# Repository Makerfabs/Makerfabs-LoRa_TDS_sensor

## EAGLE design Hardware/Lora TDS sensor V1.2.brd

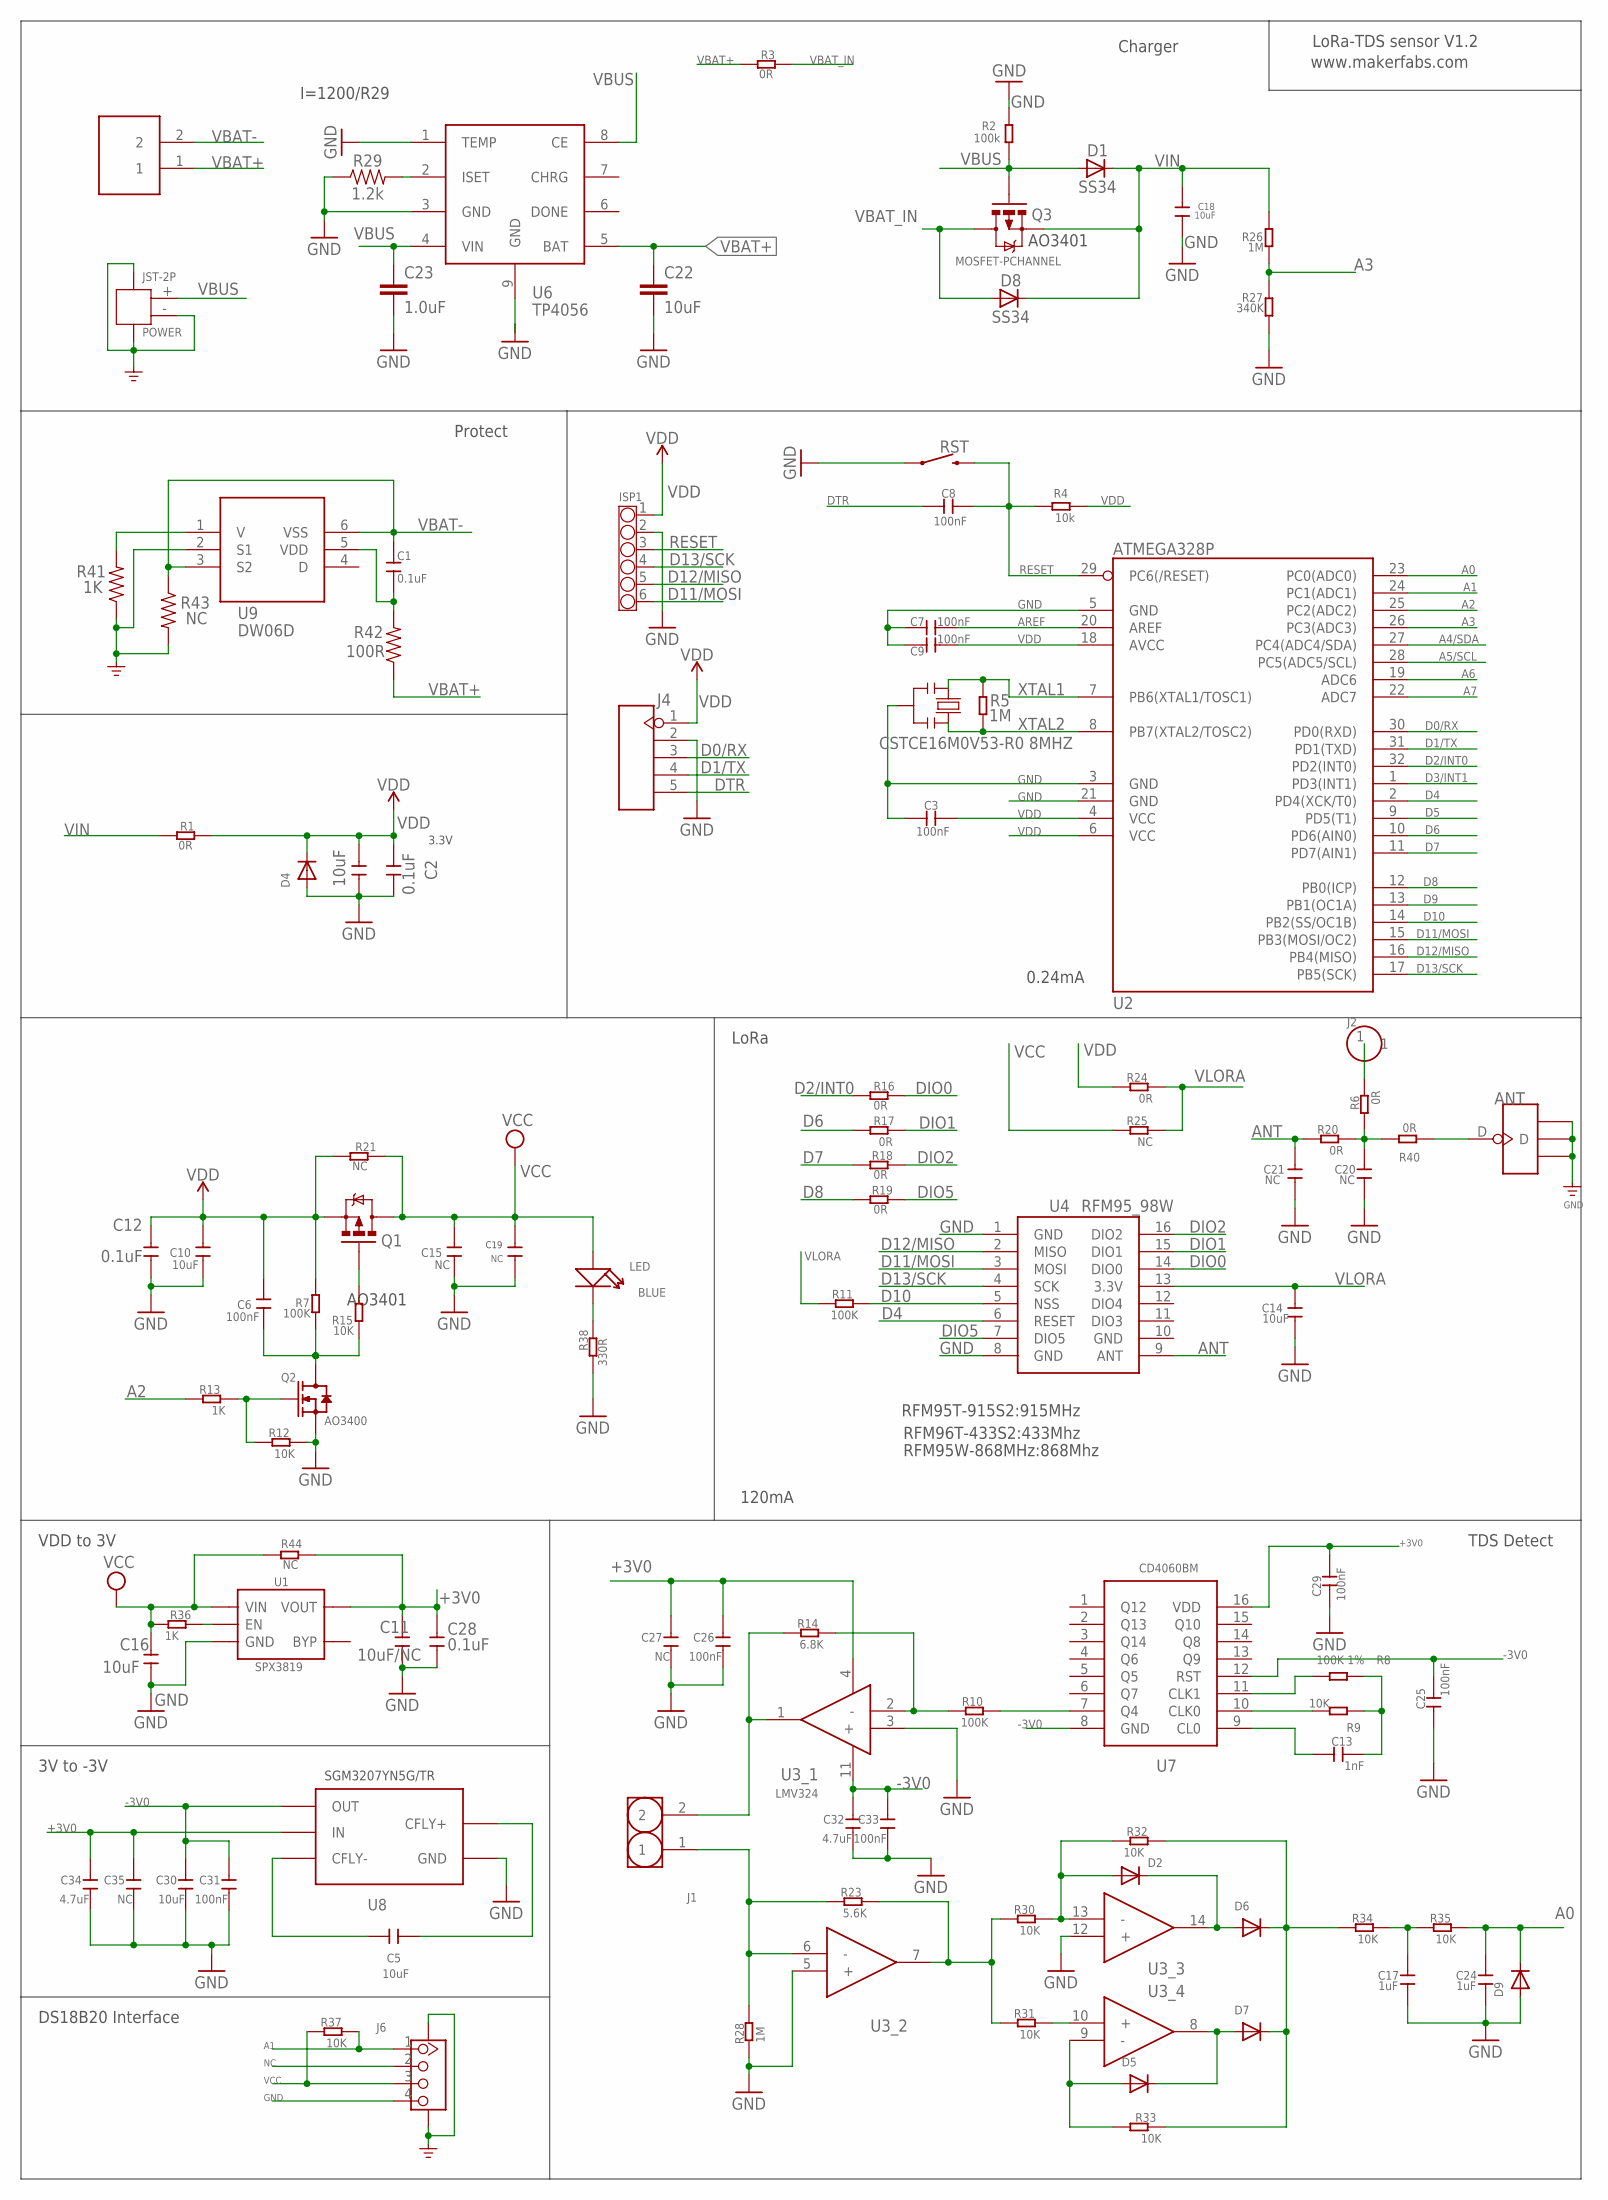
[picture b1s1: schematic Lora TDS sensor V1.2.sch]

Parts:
ANT: ANTENNA-U-FL; 4P-U-FL
C1, C2, C12, C28: 0.1uF; 0603
C3, C6, C7, C8, C9, C25, C26, C29, C31, C33: 100nF; 0603
C4, C5, C10, C14, C16, C18, C30: 10uF; 0603
C11: 10uF/NC; 0603
C13: 1nF; 0603
C15, C19, C20, C21, C27, C35: NC; 0603
C17, C24: 1uF; 0603
C22: 10uF; 1206
C23: 1.0uF; 0603
C32, C34: 4.7uF; 0603
D1, D8: SS34; DO-214AC
D2, D4, D5, D6, D7, D9: DIODESOD-323F; SOD-323F
ISP1: CONNECTOR-HEADER-6P-3460270P1; 1X6P-2.54-8.5-BLACK-FEMALE
J1: HEADER-2P-65/35MIL; 2P-2.54-65/35MIL
J2: HEADER-1P-50; 1P-100/50MIL
J4: HEADER-5P-2.54; 5P-2.54
J5: PH2.0-2P-90-DIP
J6: GROVE-CONNECTOR-SMD'90D'; HW4-SMD-2.0-90D
LED: BLUE; LED-0603
POWER: JST-2P; HW2-SMD-2.0-90D
Q1, Q3: MOSFET-PCHANNEL; SOT23-3
Q2: AO3400; DISCRETE_SOT23
R1, R3, R6, R16, R17, R18, R19, R20, R24, R40: 0R; R0603
R2: 100k; R0603
R4: 10k; R0603
R5, R26, R28: 1M; R0603
R7, R10, R11: 100K; R0603
R8: 100K 1%; R0603
R9, R12, R15, R30, R31, R32, R33, R34, R35, R37: 10K; R0603
R13, R36: 1K; R0603
R14: 6.8K; R0603
R21, R25, R44: NC; R0603
R23: 5.6K; R0603
R27: 340K; R0603
R29: 1.2k; 0603
R38: 330R; R0603
R41: 1K; 0603
R42: 100R; 0603
R43: NC; 0603
RST: MOMENTARY-SWITCH-SPST-SMD-6.0X3.5MM; TACTILE_SWITCH_SMD_6.0X3.5MM
U1: SPX3819; SOT23-5
U2: ATMEGA328P; TQFP32
U3: LM324_1; SOP-14
U4: RFM95_98W; RFM92_93W
U6: TP4056; SOP8-1.27P
U7: CD4060; SOIC-16
U8: TPS60400DBVR; SOT23-5
U9: DW06D; SOT-23-6
Y1: CSTCE16M0V53-R0 8MHZ; RESONATOR

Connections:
+3V0: C11.2, C26.2, C27.2, C28.2, C29.1, C34.2, C35.2, R44.2, U1.5 (VOUT), U3.4 (VDD), U7.16 (VDD), U8.P$2 (IN)
-3V0: C25.1, C30.2, C31.2, C32.2, C33.2, U3.11 (VSS), U7.8 (GND), U7.12 (RST), U8.P$1 (OUT)
A0: C24.2, D9.C, R35.1, U2.23 (PC0(ADC0))
A1: J6.1, R37.1, U2.24 (PC1(ADC1))
A2: R13.2, U2.25 (PC2(ADC2))
A3: R26.1, R27.2, U2.26 (PC3(ADC3))
A4/SDA: U2.27 (PC4(ADC4/SDA))
A5/SCL: U2.28 (PC5(ADC5/SCL))
A6: U2.19 (ADC6)
A7: U2.22 (ADC7)
ANT: C21.2, R20.2, U4.9 (ANT)
AREF: C7.2, U2.20 (AREF)
D0/RX: J4.3, U2.30 (PD0(RXD))
D1/TX: J4.4, U2.31 (PD1(TXD))
D2/INT0: R16.1, U2.32 (PD2(INT0))
D3/INT1: U2.1 (PD3(INT1))
D4: U2.2 (PD4(XCK/T0)), U4.6 (RESET)
D5: U2.9 (PD5(T1))
D6: R17.1, U2.10 (PD6(AIN0))
D7: R18.1, U2.11 (PD7(AIN1))
D8: R19.1, U2.12 (PB0(ICP))
D9: U2.13 (PB1(OC1A))
D10: R11.1, U2.14 (PB2(SS/OC1B)), U4.5 (NSS)
D11/MOSI: ISP1.6, U2.15 (PB3(MOSI/OC2)), U4.3 (MOSI)
D12/MISO: ISP1.5, U2.16 (PB4(MISO)), U4.2 (MISO)
D13/SCK: ISP1.4, U2.17 (PB5(SCK)), U4.4 (SCK)
DIO0: R16.2, U4.14 (DIO0)
DIO1: R17.2, U4.15 (DIO1)
DIO2: R18.2, U4.16 (DIO2)
DIO5: R19.2, U4.7 (DIO5)
DTR: C8.1, J4.5
GND: ANT.GND1, ANT.GND2, ANT.GND3, C2.1, C3.1, C4.1, C7.1, C9.1, C10.1, C11.1, C12.1, C14.1, C15.1, C16.1, C17.1, C18.1, C19.1, C20.1, C21.1, C22.2, C23.2, C24.1, C25.2, C26.1, C27.1, C28.1, C29.2, C30.1, C31.1, C32.1, C33.1, C34.1, C35.1, D4.A, D9.A, ISP1.2, J4.2, J6.4, J6.SS1, J6.SS2, POWER.3, POWER.4, POWER.- (2), Q2.2 (S), R2.2, R12.1, R27.1, R28.2, R29.1, R38.2, R41.1, R43.2, RST.1, U1.2 (GND), U2.3 (GND), U2.5 (GND), U2.21 (GND), U3.3 (+), U3.5 (+), U3.12 (+), U4.1 (GND), U4.8 (GND), U4.10 (GND), U6.1 (TEMP), U6.3 (GND), U6.9 (GND), U8.P$4 (GND), U9.2 (S1), Y1.2
ISET: R29.2, U6.2 (ISET)
unnamed: C1.2, R42.2, U9.5 (VDD)
unnamed: R36.2, U1.3 (EN)
unnamed: LED.-, R38.1
unnamed: R8.1, U7.11 (CLK1)
unnamed: R9.1, U7.10 (CLK0)
unnamed: J2.1, R6.1
unnamed: Q1.1 (G), R15.2
unnamed: C6.1, Q2.3 (D), R7.1, R15.1
unnamed: C13.2, U7.9 (CL0)
unnamed: Q2.1 (G), R12.2, R13.1
unnamed: C13.1, R8.2, R9.2
unnamed: C20.2, R6.2, R20.1, R40.1
unnamed: R41.2, U9.1 (V)
unnamed: C5.2, U8.P$3 (CFLY-)
unnamed: R10.1, U7.7 (Q4)
unnamed: C5.1, U8.P$5 (CFLY+)
unnamed: R10.2, R14.1, U3.2 (-)
unnamed: J1.2, R14.2, U3.1 (OUT)
unnamed: J1.1, R23.2, R28.1, U3.6 (-)
unnamed: R23.1, R30.2, R31.2, U3.7 (OUT)
unnamed: D2.A, R30.1, R32.2, U3.13 (-)
unnamed: D2.C, D6.A, U3.14 (OUT)
unnamed: R31.1, U3.10 (+)
unnamed: D6.C, D7.C, R32.1, R33.1, R34.2
unnamed: D5.A, R33.2, U3.9 (-)
unnamed: D5.C, D7.A, U3.8 (OUT)
unnamed: ANT.D, R40.2
unnamed: C17.2, R34.1, R35.2
NC: J6.2
RESET: C8.2, ISP1.3, R4.2, RST.2, U2.29 (PC6(/RESET))
VBAT+: C22.1, J5.1, R3.2, R42.1, U6.5 (BAT)
VBAT-: C1.1, J5.2, R43.1, U9.3 (S2), U9.6 (VSS)
VBAT_IN: D8.A, Q3.3 (D), R3.1
VBUS: C23.1, D1.A, POWER.+ (1), Q3.1 (G), R2.1, U6.4 (VIN), U6.8 (CE)
VCC: C15.2, C16.2, C19.2, J6.3, LED.+, Q1.3 (D), R21.1, R25.2, R36.1, R37.2, R44.1, U1.1 (VIN)
VDD: C2.2, C3.2, C4.2, C6.2, C9.2, C10.2, C12.2, D4.C, ISP1.1, J4.1, Q1.2 (S), R1.1, R4.1, R7.2, R21.2, R24.2, U2.4 (VCC), U2.6 (VCC), U2.18 (AVCC)
VIN: C18.2, D1.C, D8.C, Q3.2 (S), R1.2, R26.2
VLORA: C14.2, R11.2, R24.1, R25.1, U4.13 (3.3V)
XTAL1: R5.2, U2.7 (PB6(XTAL1/TOSC1)), Y1.1
XTAL2: R5.1, U2.8 (PB7(XTAL2/TOSC2)), Y1.3

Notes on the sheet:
RFM95T-915S2:915MHz
RFM96T-433S2:433Mhz
RFM95W-868MHz:868Mhz
www.makerfabs.com
AO3401
I=1200/R29
Charger
3.3V
LoRa-TDS sensor V1.2
SGM3207YN5G/TR
0.24mA
120mA
Protect
VDD to 3V
3V to -3V
DS18B20 Interface
LoRa
TDS Detect

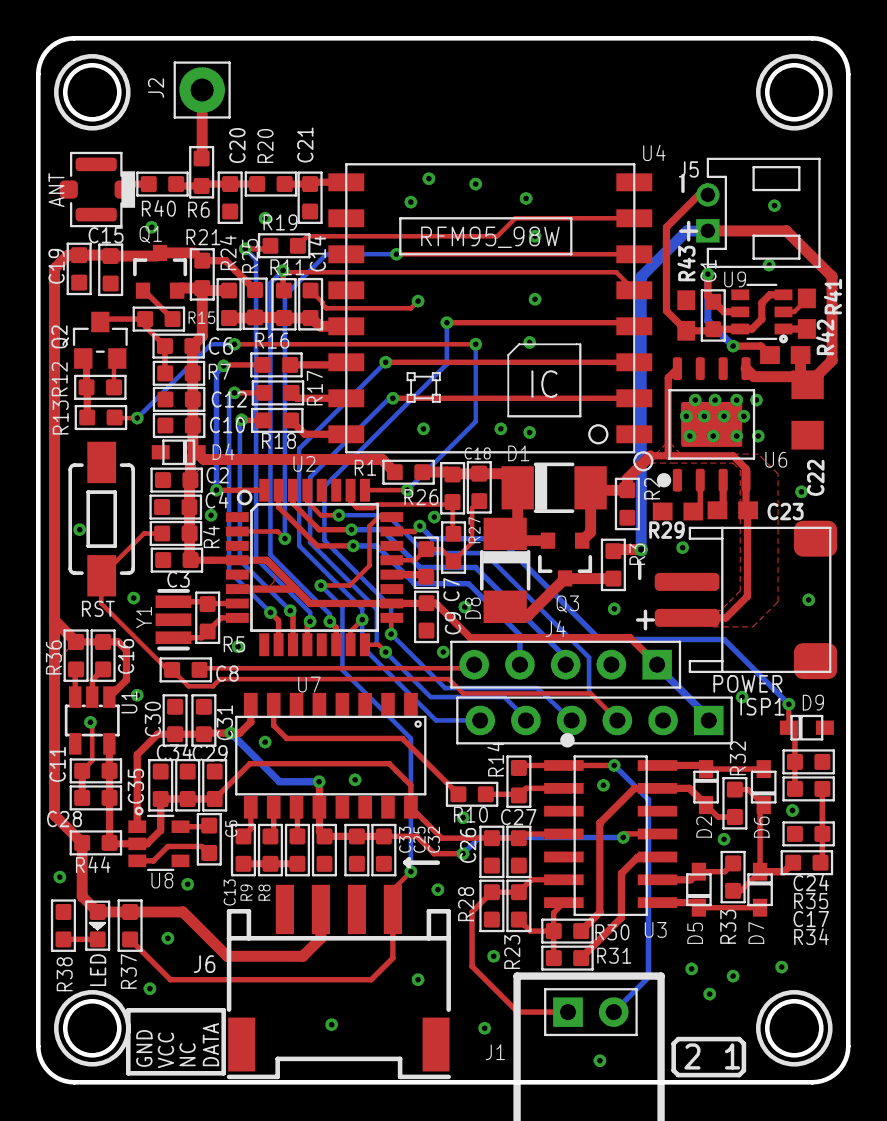
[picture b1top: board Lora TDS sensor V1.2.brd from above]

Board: 2 copper layers, 45.0 x 58.0 mm, 108 parts (1 on the bottom side), 65 nets.

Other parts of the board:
U$2: MAKERFABS_0.3

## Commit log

2021-09-17 Create hardware, firmware
2021-09-17 Create transmit demo
2021-09-17 update transmitter
2021-10-28 Create Lora receiver

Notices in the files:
parts and their libraries:
User-Submitted: Licensing: Creative Commons ShareAlike 4.0 International - https://creativecommons.org/licenses/by-sa/4.0
